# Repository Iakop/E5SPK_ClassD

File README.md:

# E5SPK_ClassD
Class D Amplifier project for the 5th semester course, Switched Power Circuits. By Jacob Bechmann Pedersen and Mikkel Bjerg Petersen.

## Tools 
- The project calculations are alle done in MathCAD Prime
  - but might be converted to another format if needed
- The simulations are done in LTSpice
- Schematics and board layout are done in KiCad

## Key Components
- UCC27201 - 120V bootstrap Half H Driver
- LM360 - 5V High-speed comparator
- IPD180N10N3 - 43A 100V 33mΩ MOSFET DPAK
- BZX84C5V6 - 5.6V Zener Diode
- LM833 - Dual Audio OpAmp
- IES101-4 - TRS Jack connector
- ECA1HM222 - Electorlytic 2200uF Capacitor against supply pumping

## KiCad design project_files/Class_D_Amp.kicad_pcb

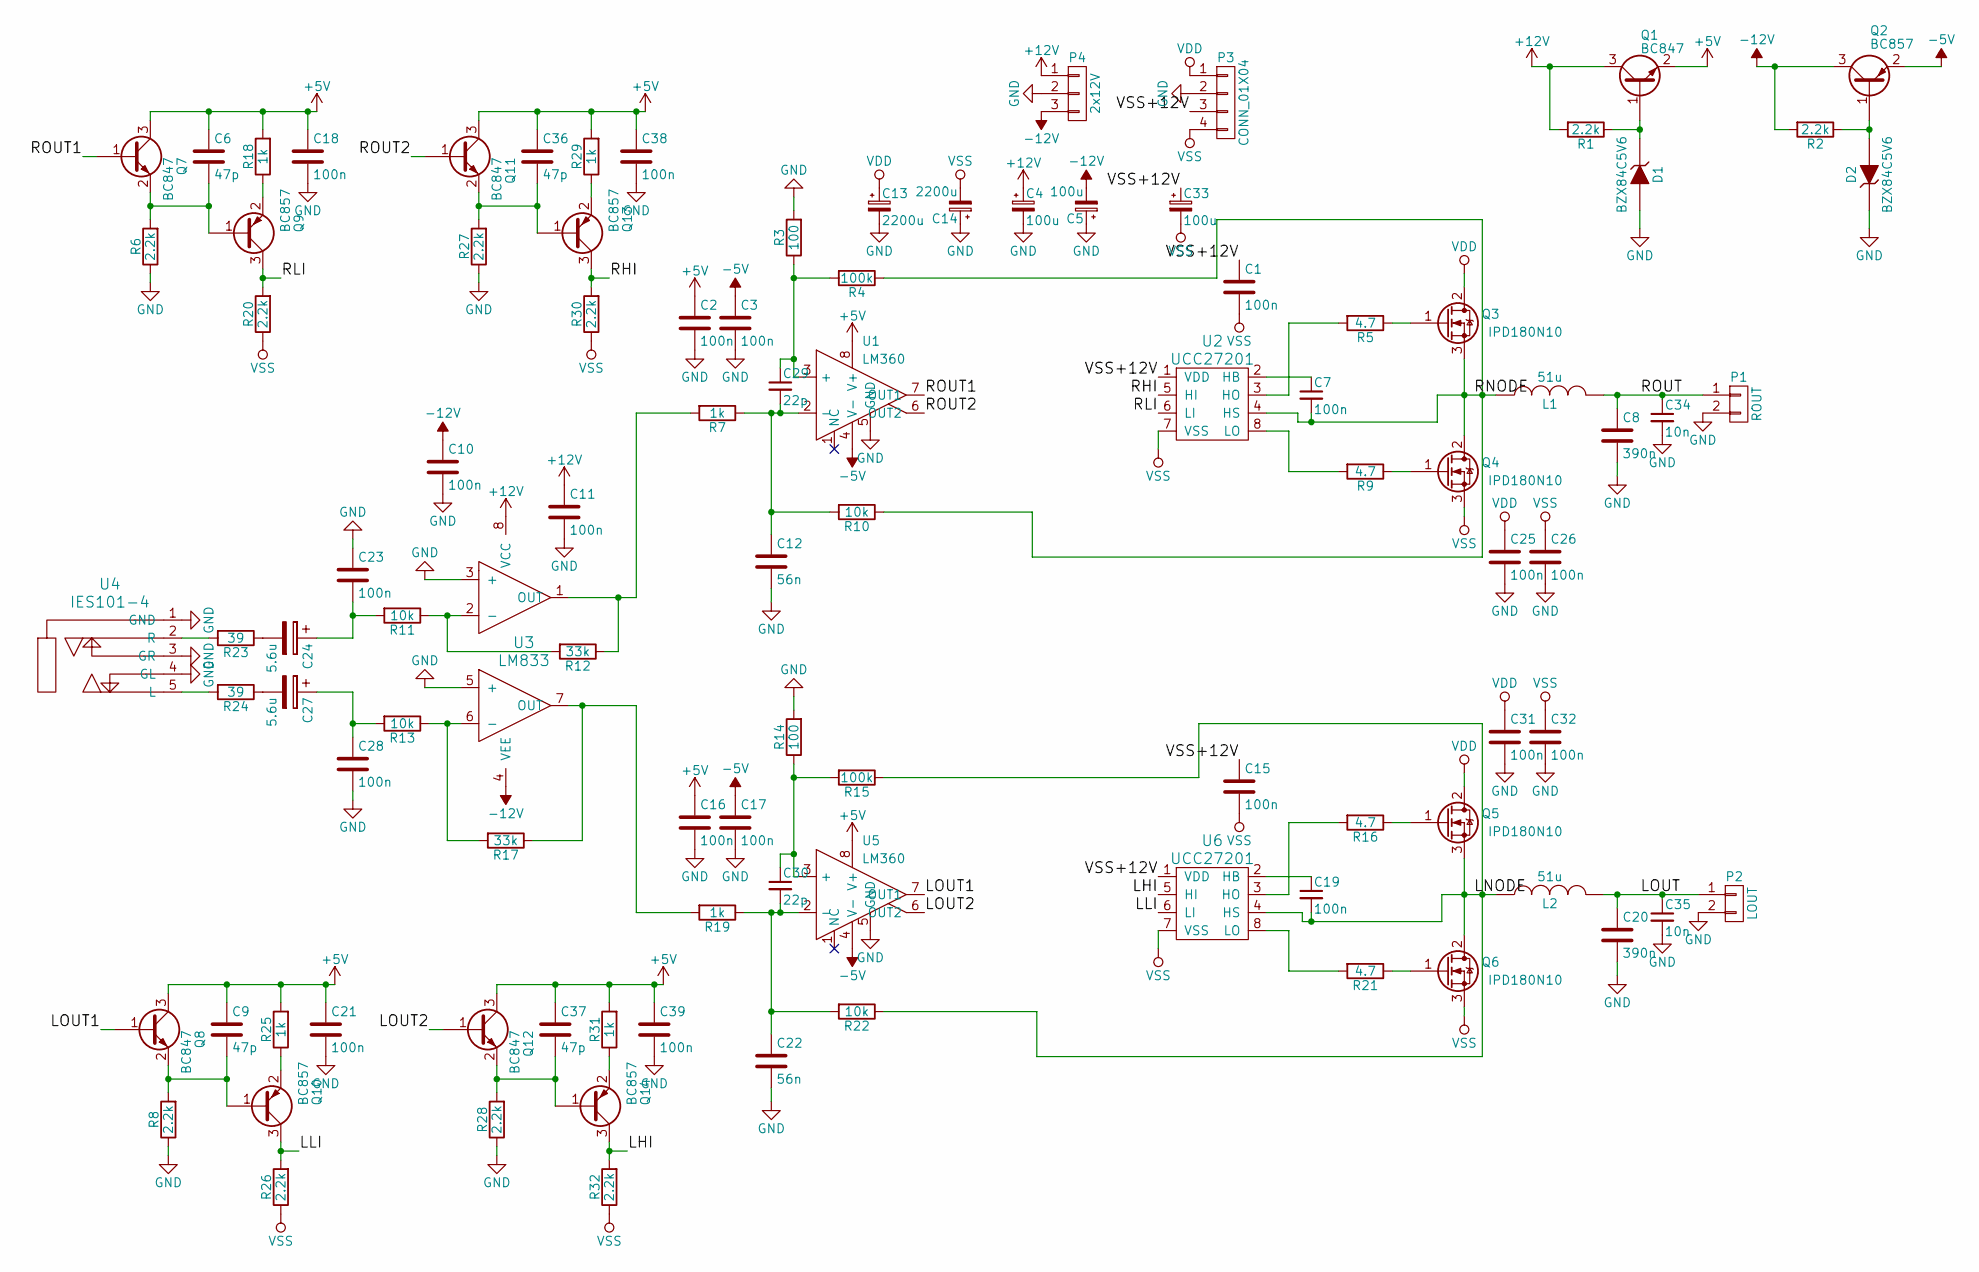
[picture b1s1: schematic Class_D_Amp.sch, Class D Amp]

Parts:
C1, C2, C3, C7, C10, C11, C15, C16, C17, C18, C19, C21, C23, C25, C26, C28, C31, C32, C38, C39: 100n; C_0805
C4, C5, C33: 100u; CP_Radial_D6.3mm_P2.50mm
C6, C9, C36, C37: 47p; C_0805
C8, C20: 390n; C_Rect_L7.0mm_W3.5mm_P5.00mm
C12, C22: 56n; C_0805
C13, C14: 2200u; CP_Radial_D16.0mm_P7.50mm
C24, C27: 5.6u; CP_Radial_D5.0mm_P2.00mm
C29, C30: 22p; C_0805
C34, C35: 10n; C_0805
D1, D2: BZX84C5V6; SOT-23
L1, L2: 51u; 3C20
P1: ROUT; TerminalBlock_bornier-2_P5.08mm
P2: LOUT; TerminalBlock_bornier-2_P5.08mm
P3: CONN_01X04; TerminalBlock_bornier-4_P5.08mm
P4: 2x12V; TerminalBlock_bornier-3_P5.08mm
Q1, Q7, Q8, Q11, Q12: BC847; SOT-23
Q2, Q9, Q10, Q13, Q14: BC857; SOT-23
Q3, Q4, Q5, Q6: IPD180N10; TO-252-2
R1, R2, R6, R8, R20, R26, R27, R28, R30, R32: 2.2k; R_0805
R3, R14: 100; R_0805
R4, R15: 100k; R_0805
R5, R9, R16, R21: 4.7; R_1206
R7, R18, R19, R25, R29, R31: 1k; R_0805
R10, R11, R13, R22: 10k; R_0805
R12, R17: 33k; R_0805
R23, R24: 39; R_0805
U1, U5: LM360; SOIC-8_3.9x4.9mm_Pitch1.27mm
U2, U6: UCC27201; SOIC-8_3.9x4.9mm_Pitch1.27mm
U3: LM833; SOIC-8_3.9x4.9mm_Pitch1.27mm
U4: IES101-4; Stereo_Jack_3.5mm_Switch_Ledino_KB3SPRS

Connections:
+5V: C2.1, C6.1, C9.1, C16.1, C18.1, C21.1, C36.1, C37.1, C38.1, C39.1, Q1.2 (E), Q7.3 (C), Q8.3 (C), Q11.3 (C), Q12.3 (C), R18.2, R25.2, R29.2, R31.2, U1.8 (V+), U5.8 (V+)
+12V: C4.1, C11.1, P4.1, Q1.3 (C), R1.2, U3.8 (VCC)
-5V: C3.1, C17.1, Q2.2 (E), U1.4 (V-), U5.4 (V-)
-12V: C5.2, C10.1, P4.3, Q2.3 (C), R2.2, U3.4 (VEE)
/LHI: Q14.3 (C), R32.2, U6.5 (HI)
/LLI: Q10.3 (C), R26.2, U6.6 (LI)
/LNODE: C19.2, L2.1, Q5.3 (S), Q6.2 (D), R15.1, R22.1, U6.4 (HS)
/LOUT: C20.1, C35.1, L2.2, P2.1
/LOUT1: Q8.1 (B), U5.7 (OUT1)
/LOUT2: Q12.1 (B), U5.6 (OUT2)
/RHI: Q13.3 (C), R30.2, U2.5 (HI)
/RLI: Q9.3 (C), R20.2, U2.6 (LI)
/RNODE: C7.2, L1.1, Q3.3 (S), Q4.2 (D), R4.1, R10.1, U2.4 (HS)
/ROUT: C8.1, C34.1, L1.2, P1.1
/ROUT1: Q7.1 (B), U1.7 (OUT1)
/ROUT2: Q11.1 (B), U1.6 (OUT2)
/VSS+12V: C1.1, C15.1, C33.1, P3.3, U2.1 (VDD), U6.1 (VDD)
GND: C2.2, C3.2, C4.2, C5.1, C8.2, C10.2, C11.2, C12.2, C13.2, C14.1, C16.2, C17.2, C18.2, C20.2, C21.2, C22.2, C23.1, C25.2, C26.2, C28.2, C31.2, C32.2, C34.2, C35.2, C38.2, C39.2, D1.1 (A), D2.3 (K), P1.2, P2.2, P3.2, P4.2, R3.2, R6.1, R8.1, R14.2, R27.1, R28.1, U1.5 (GND), U3.3 (+), U3.5 (+), U4.1 (GND), U4.3 (GR), U4.4 (GL), U5.5 (GND)
unnamed: C6.2, Q7.2 (E), Q9.1 (B), R6.2
unnamed: C7.1, U2.2 (HB)
unnamed: C9.2, Q8.2 (E), Q10.1 (B), R8.2
unnamed: C12.1, C29.2, R7.1, R10.2, U1.2 (-)
unnamed: C19.1, U6.2 (HB)
unnamed: C22.1, C30.2, R19.1, R22.2, U5.2 (-)
unnamed: C23.2, C24.1, R11.2
unnamed: C24.2, R23.1
unnamed: C27.1, C28.1, R13.2
unnamed: C27.2, R24.1
unnamed: C29.1, R3.1, R4.2, U1.3 (+)
unnamed: C30.1, R14.1, R15.2, U5.3 (+)
unnamed: C36.2, Q11.2 (E), Q13.1 (B), R27.2
unnamed: C37.2, Q12.2 (E), Q14.1 (B), R28.2
unnamed: D1.3 (K), Q1.1 (B), R1.1
unnamed: D2.1 (A), Q2.1 (B), R2.1
unnamed: Q3.1 (G), R5.1
unnamed: Q4.1 (G), R9.1
unnamed: Q5.1 (G), R16.1
unnamed: Q6.1 (G), R21.1
unnamed: Q9.2 (E), R18.1
unnamed: Q10.2 (E), R25.1
unnamed: Q13.2 (E), R29.1
unnamed: Q14.2 (E), R31.1
unnamed: R5.2, U2.3 (HO)
unnamed: R9.2, U2.8 (LO)
unnamed: R11.1, R12.2, U3.2 (-)
unnamed: R7.2, R12.1, U3.1 (OUT)
unnamed: R13.1, R17.2, U3.6 (-)
unnamed: R16.2, U6.3 (HO)
unnamed: R17.1, R19.2, U3.7 (OUT)
unnamed: R21.2, U6.8 (LO)
unnamed: R23.2, U4.2 (R)
unnamed: R24.2, U4.5 (L)
VDD: C13.1, C25.1, C31.1, P3.1, Q3.2 (D), Q5.2 (D)
VSS: C1.2, C14.2, C15.2, C26.1, C32.1, C33.2, P3.4, Q4.3 (S), Q6.3 (S), R20.1, R26.1, R30.1, R32.1, U2.7 (VSS), U6.7 (VSS)

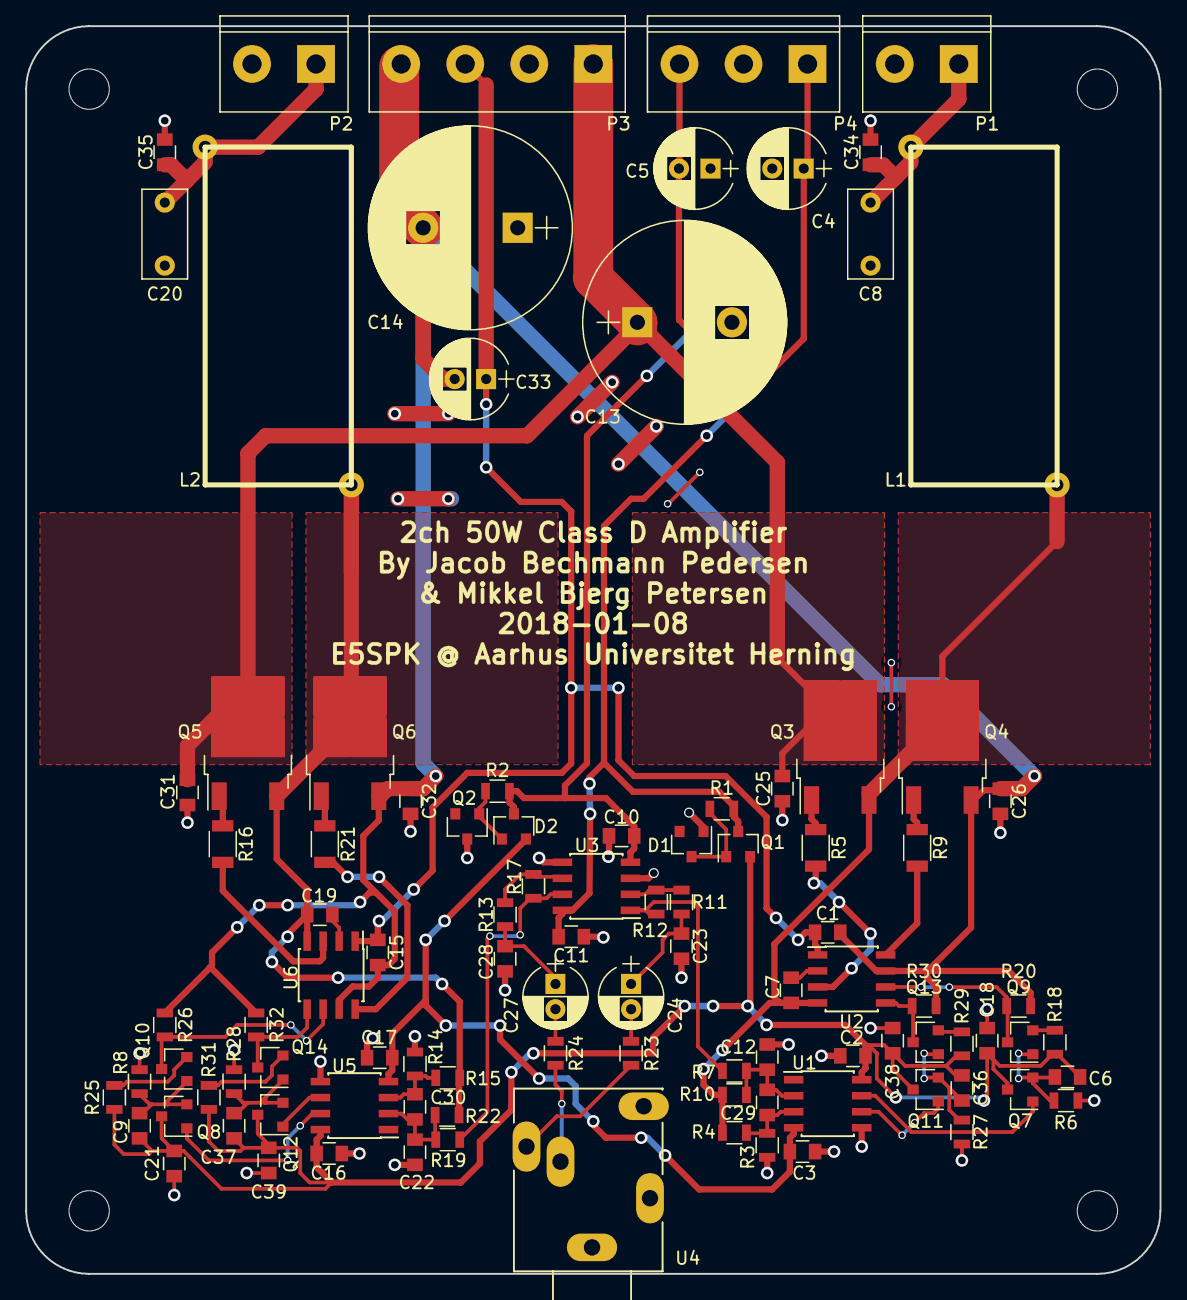
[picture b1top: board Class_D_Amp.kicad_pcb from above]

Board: 2 copper layers, 90.0 x 99.0 mm, 99 parts (0 on the bottom side), 54 nets.

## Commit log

2017-12-01 :boom::camel: Added .gitattributes
2017-12-01 Added KiCad Schematics and PCB
2017-12-01 Created README.md
2017-12-01 First Schematic Version
2017-12-07 Minor updates
2017-12-08 Fixed Issues in Schematic + Generated netlist
    Changed feedback to come from output nodes.
    Fixed Driver supplies
    Added global decoupling
    Hopefully fixed supply pumping
2017-12-08 Minor fix
2017-12-15 Updated schematic and netlist
2017-12-15 Clustered modules together
2017-12-15 Updated PCB design
2017-12-18 Fixed Thermal pads
2017-12-22 Completed first revision of board
2017-12-22 Fixed schematic name
2017-12-23 Generated Gerbers
2017-12-23 fixed size
2017-12-26 Added the Level Shifters to Schematic
2017-12-26 Plotted Schematic PDF
2017-12-27 Completed Board Layout
